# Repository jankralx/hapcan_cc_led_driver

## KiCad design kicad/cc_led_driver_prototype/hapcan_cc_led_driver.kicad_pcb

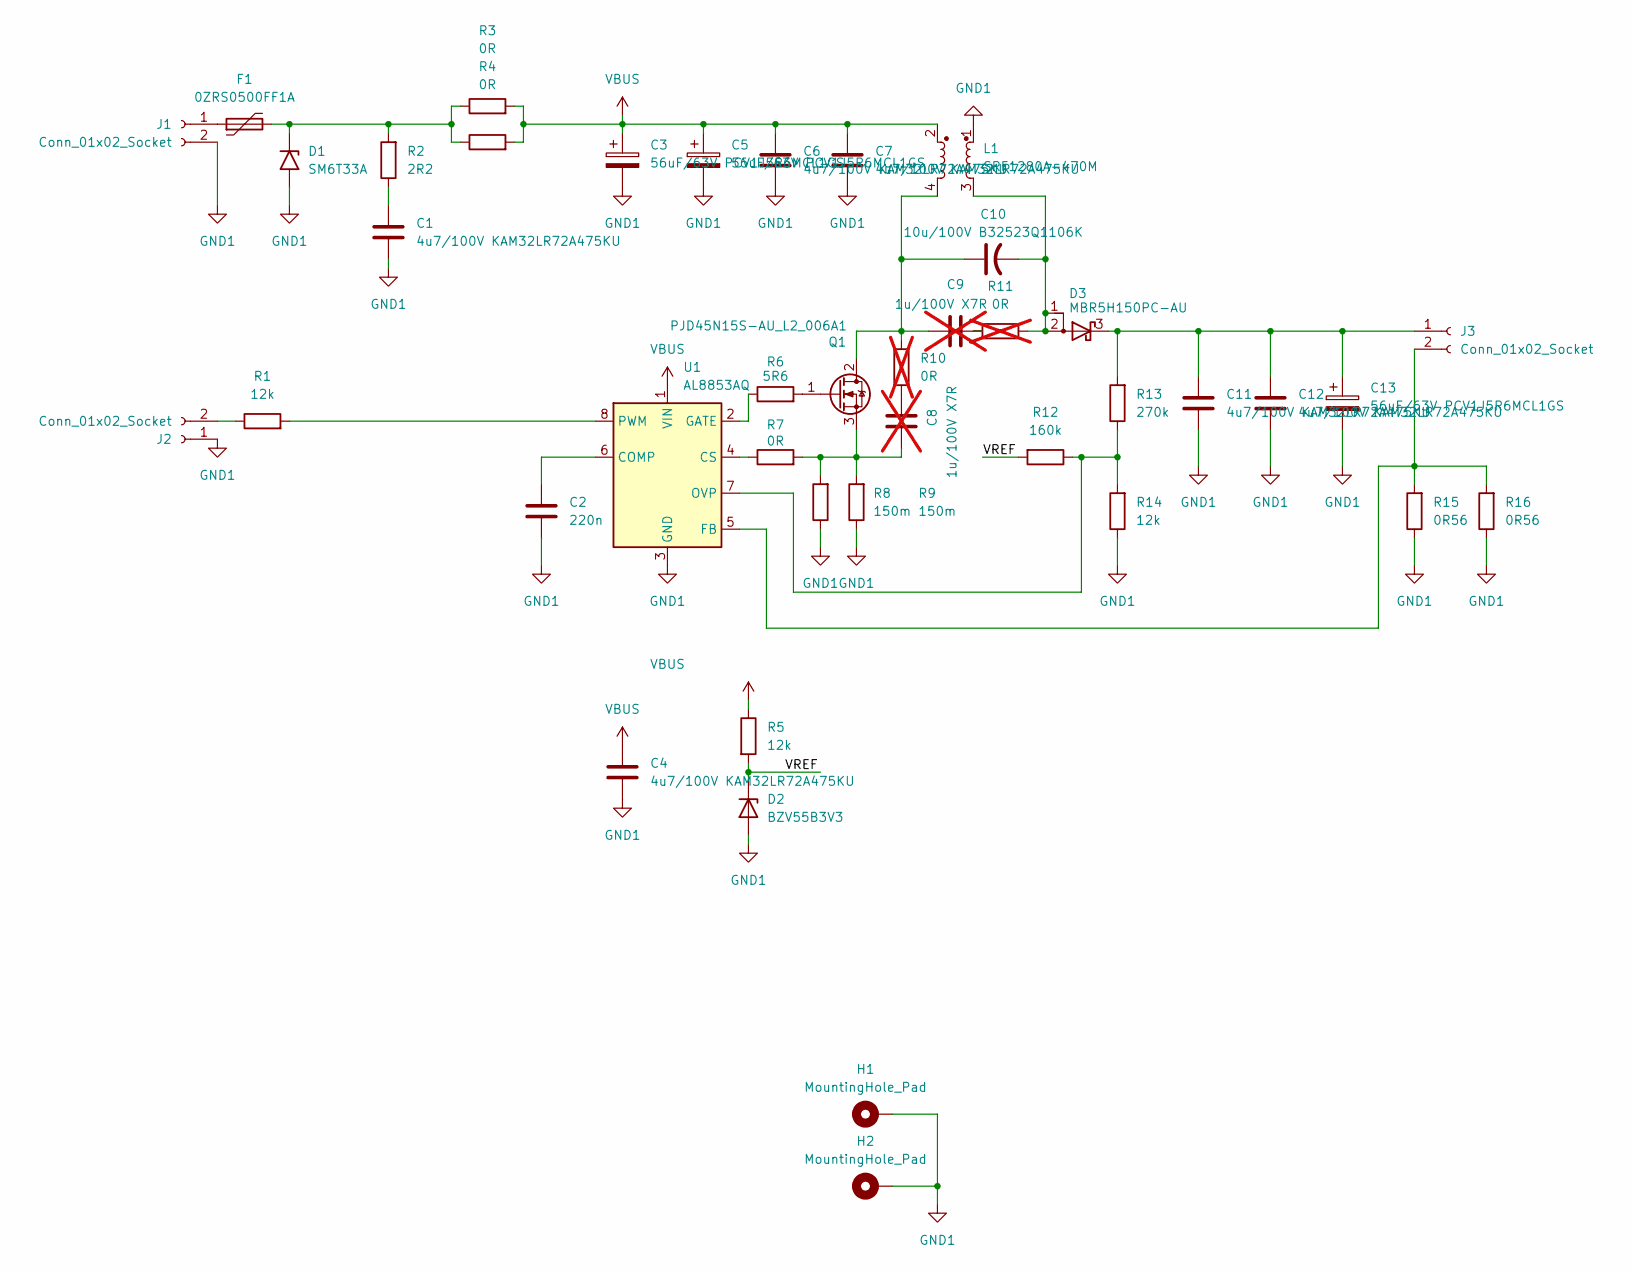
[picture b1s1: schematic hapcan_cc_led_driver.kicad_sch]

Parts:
C1, C4, C6, C7, C11, C12: 4u7/100V KAM32LR72A475KU; C_1210_3225Metric
C2: 220n; C_0805_2012Metric
C3, C5, C13: 56uF/63V PCV1J5R6MCL1GS; C_Elec_6.3x5.8
C8, C9: 1u/100V X7R; C_1210_3225Metric; not fitted
C10: 10u/100V B32523Q1106K; C_Rect_L28.0mm_W10.0mm_P22.50mm_MKS4
D1: SM6T33A; D_SMB
D2: BZV55B3V3; D_MiniMELF
D3: MBR5H150PC-AU; TO-277A
F1: 0ZRS0500FF1A; C_Disc_D9.0mm_W2.5mm_P5.00mm
H1, H2: MountingHole_Pad; MountingHole_3.2mm_M3_Pad_Via
J1, J3: Conn_01x02_Socket; PhoenixContact_MSTBA_2,5_2-G-5,08_1x02_P5.08mm_Horizontal
J2: Conn_01x02_Socket; PinHeader_1x02_P2.54mm_Vertical
L1: SRF1280A-470M; L_CommonModeChoke_Bourns_SRF1260
Q1: PJD45N15S-AU_L2_006A1; TO-252-2
R1, R5, R14: 12k; R_0805_2012Metric
R2: 2R2; R_0805_2012Metric
R3, R4: 0R; R_1210_3225Metric_Pad1.30x2.65mm_HandSolder
R6: 5R6; R_0805_2012Metric
R7: 0R; R_0805_2012Metric
R8, R9: 150m; R_1206_3216Metric
R10: 0R; R_1210_3225Metric_Pad1.30x2.65mm_HandSolder; not fitted
R11: 0R; R_0805_2012Metric; not fitted
R12: 160k; R_0805_2012Metric
R13: 270k; R_0805_2012Metric
R15, R16: 0R56; R_1206_3216Metric
U1: AL8853AQ; SO-8_3.9x4.9mm_P1.27mm

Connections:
/VREF: D2.1 (K), R5.2, R12.2
GND1: C1.2, C2.2, C3.2, C4.2, C5.2, C6.2, C7.2, C11.2, C12.2, C13.2, D1.2 (A2), D2.2 (A), H1.1 (1_1), H2.1, J1.2, J2.1, L1.1, R8.1, R9.1, R14.1, R15.1, R16.1, U1.3 (GND)
unnamed: C1.1, R2.1
unnamed: C8.2, R10.2
unnamed: C9.2, R11.2
unnamed: C10.2, D3.1 (A), D3.2 (A), L1.3, R11.1
unnamed: D1.1 (A1), F1.2, R2.2, R3.1, R4.1
unnamed: C11.1, C12.1, C13.1, D3.3 (K), J3.1, R13.2
unnamed: F1.1, J1.1
unnamed: J2.2, R1.1
unnamed: J3.2, R15.2, R16.2, U1.5 (FB)
unnamed: C9.1, C10.1, L1.4, Q1.2 (D), R10.1
unnamed: Q1.1 (G), R6.2
unnamed: C8.1, Q1.3 (S), R7.2, R8.2, R9.2
unnamed: C2.1, U1.6 (COMP)
unnamed: R7.1, U1.4 (CS)
unnamed: R6.1, U1.2 (GATE)
unnamed: R12.1, R13.1, R14.2, U1.7 (OVP)
unnamed: R1.2, U1.8 (PWM)
VBUS: C3.1, C4.1, C5.1, C6.1, C7.1, L1.2, R3.2, R4.2, R5.1, U1.1 (VIN)

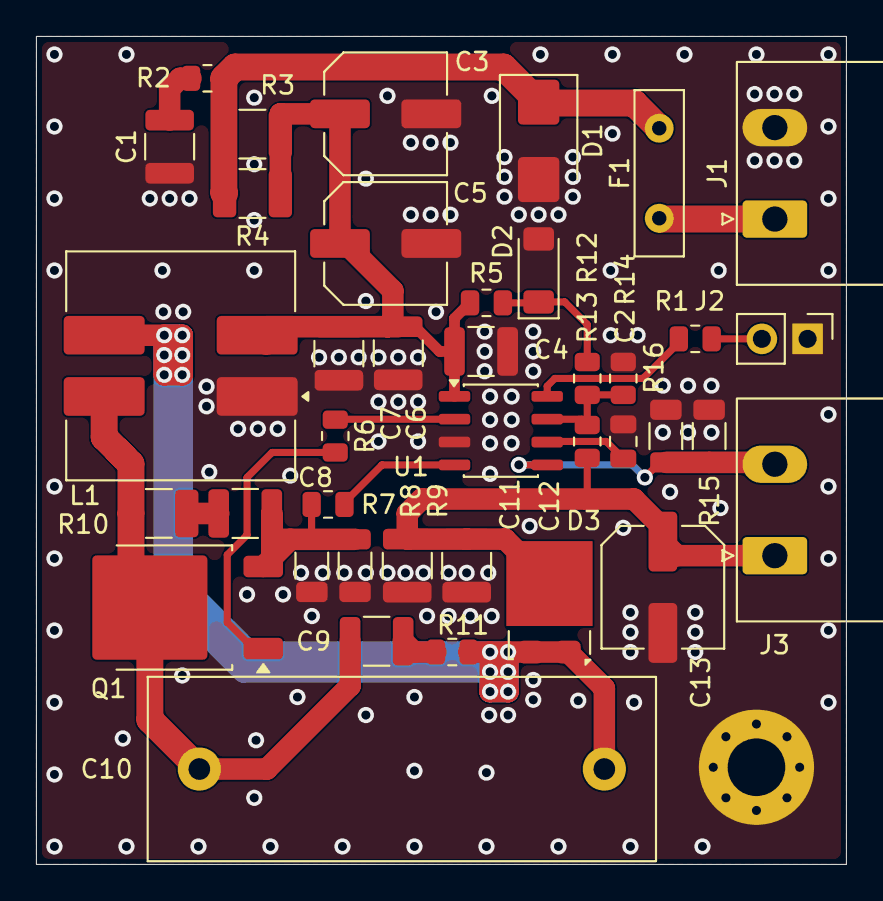
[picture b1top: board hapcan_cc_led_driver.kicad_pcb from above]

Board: 4 copper layers, 45.0 x 46.0 mm, 40 parts (0 on the bottom side), 20 nets.
